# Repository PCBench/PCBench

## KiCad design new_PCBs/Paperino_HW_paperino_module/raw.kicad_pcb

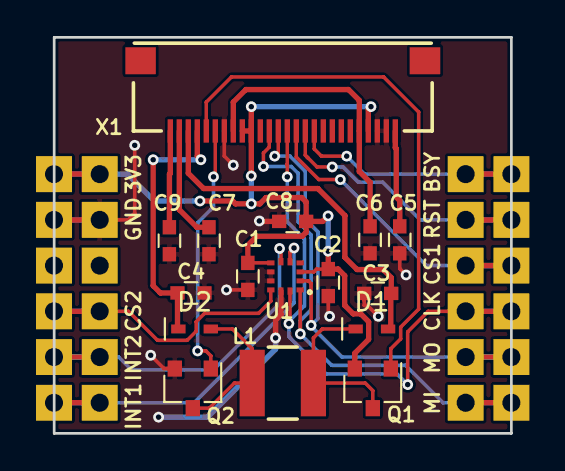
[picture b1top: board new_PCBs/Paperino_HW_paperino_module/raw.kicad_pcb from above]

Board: 2 copper layers, 25.4 x 22.0 mm, 20 parts (0 on the bottom side), 21 nets.

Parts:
C1, C2, C5: 100n; C_0603
C3, C4: 2µ2; C_0603
C6, C7, C8, C9: 1µ; C_0603
D1, D2: 30V; SOD-523F
L1: 47µ; NR4018T470M
P1, P2, P3, P4: CONN_01X06; 1x6_header
Q1: PMOS; SOT-23
Q2: NMOS; SOT-23
U1: BMA250E; LGA-12-2x2x0.95
X1: XF2M-2615-1A

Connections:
+3V3: C1.1, C2.2, C8.1, P2.1, P4.1, Q1.2, U1.3, U1.7, X1.4, X1.17, X1.18
/GDR_N: Q2.1, X1.21
/GDR_P: Q1.1, X1.22
/INT1: P2.6, P4.6, U1.5
/INT2: P2.5, P4.5, U1.6
/SPI_CLK: P1.3, P3.3, U1.12, X1.13
/SPI_CS1: P1.4, P3.4, X1.12
/SPI_CS2: P2.4, P4.4, U1.10
/SPI_MISO: P1.1, P3.1, U1.1, X1.15
/SPI_MOSI: P1.2, P3.2, U1.2, X1.14
/TPCOM: C5.1, X1.1
/VDD: C6.1, X1.5, X1.19
/VGH: C4.2, D2.1, X1.23
/VGL: C3.1, D1.2, X1.24
/VSH: C7.1, X1.25
/VSL: C9.1, X1.26
/~BUSY: P1.6, P3.6, X1.10
/~RST: P1.5, P3.5, X1.11
GND: C1.2, C2.1, C3.2, C4.1, C5.2, C6.2, C7.2, C8.2, C9.2, P2.2, P4.2, Q2.2, U1.8, U1.9, U1.11, X1.2, X1.3, X1.20
unnamed: D1.1, L1.1, Q1.3
unnamed: D2.2, L1.2, Q2.3

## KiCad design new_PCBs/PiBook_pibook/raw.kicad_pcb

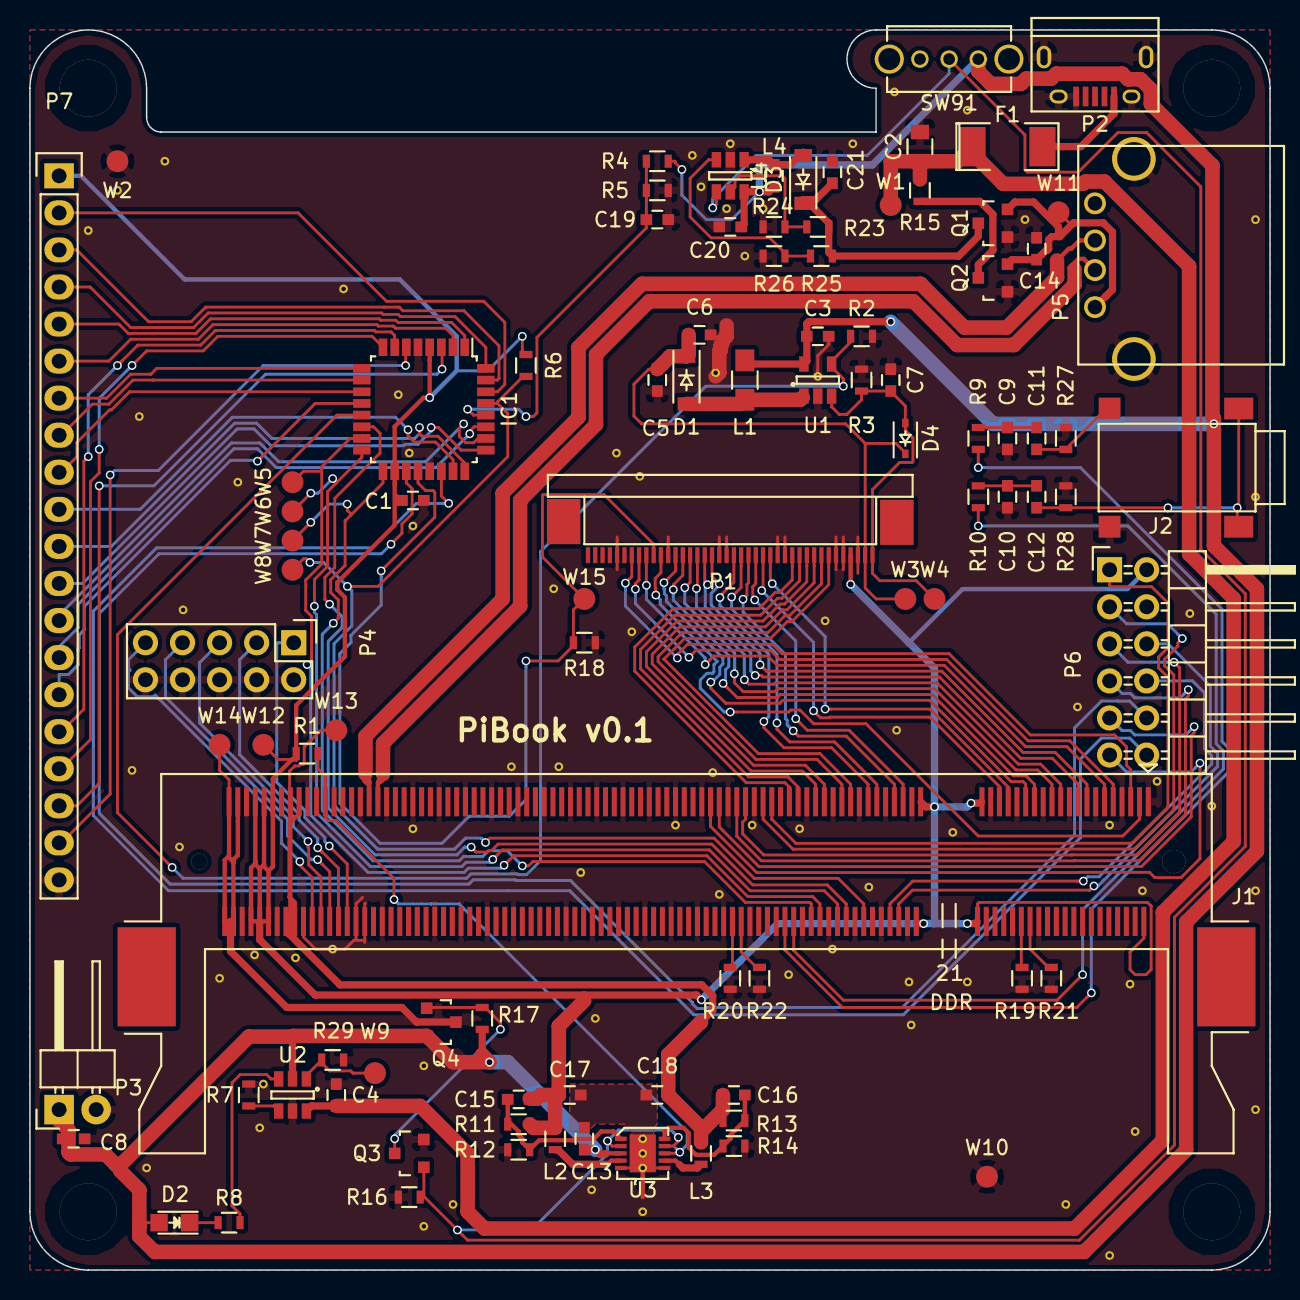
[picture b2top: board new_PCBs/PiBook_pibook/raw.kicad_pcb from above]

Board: 2 copper layers, 85.0 x 85.0 mm, 98 parts (0 on the bottom side), 103 nets.

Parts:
C1, C4, C5, C6, C7, C8, C11, C12, C20, C21: 1u; C_0603
C2: 22u; C_0805
C3: 4.7u; C_0603
C9, C10: 82n; C_0603
C13, C14, C17, C18: 10u; C_0603
C15, C16: 18p; C_0603
C19: 100n; C_0603
D1, D3: MBR0540T3G; SOD-123
D2: LED; LED_0805
D4: MM32Z24VT1G; SOD-323
F1: 2A; SMD-2010_Pol
IC1: ATTINY48-A; LQFP-32_7x7mm_Pitch0.8mm
J1: ComputeModule; Socket_SODIMM_DDR1-2_TE_1612618
J2: TRS_JACK_3PIN; TRS_3_SMD
L1: 6.8u; R_0805_HandSoldering
L2, L3: 2.2u; R_0603
L4: 10u; C_0603
MH1, MH2, MH3, MH4: Mounting_Hole; Mounting_hole_M3.5
P1: CONN_01X40; FPC40_BOTTOM
P2: USB_OTG; USB_Micro-B
P3: CONN_01X02; Pin_Header_Angled_1x02
P4: CONN_02X05; Pin_Header_Straight_2x05
P5: USB_A
P6: CONN_02X06; Pin_Header_Angled_2x06
P7: CONN_01X20; Pin_Header_Straight_1x20
Q1, Q2, Q4: Si2323DS; SOT-23
Q3: BSS138P; SOT-23
R1, R2, R4, R5, R6, R12, R14, R16, R17, R18, R19, R20, R21, R22, R27, R28: 100k; R_0603
R3: 12; R_0603
R7: 680; R_0603
R8: R; R_0603
R9, R10: 100; R_0603
R11: 450k; R_0603
R13: 200k; R_0603
R15: 0; R_0603
R23: 47k; R_0603
R24, R26, R29: 10k; R_0603
R25: 40k; R_0603
SW91: SPST; SPDT_SLIDE_SWITCH
TP1: Tie_point; tiepoint-0.3
U1: FAN5333; SOT-23-5
U2: BQ21040; SOT-23-6
U3: NCP1532; UDFN-10
U4: MIC2619YD6; SOT-23-6
W1: USB_VIN+; Measurement_Point_Round-SMD-Pad_Small
W2: USB_VIN-; Measurement_Point_Round-SMD-Pad_Small
W3: BACKL_A; Measurement_Point_Round-SMD-Pad_Small
W4: BACKL_K; Measurement_Point_Round-SMD-Pad_Small
W5, W6, W7, W8, W15: TEST_1P; Measurement_Point_Round-SMD-Pad_Small
W9: TS; Measurement_Point_Round-SMD-Pad_Small
W10: GND; Measurement_Point_Round-SMD-Pad_Small
W11: VUSB_OUT; Measurement_Point_Round-SMD-Pad_Small
W12: +3V3; Measurement_Point_Round-SMD-Pad_Small
W13: +1V8; Measurement_Point_Round-SMD-Pad_Small
W14: CM_VBAT; Measurement_Point_Round-SMD-Pad_Small

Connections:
+1V8: C16.1, C18.1, J1.183, J1.184, J1.185, J1.186, L3.2, R13.1, W13.1
+3V3: C1.1, C15.1, C17.1, IC1.4, IC1.18, J1.2, J1.39, J1.40, J1.41, J1.42, J1.189, J1.190, J1.191, J1.192, J1.193, J1.194, L2.2, P1.4, P6.2, P7.1, R1.1, R6.1, R11.1, W12.1
+5V: C21.1, D3.1, Q1.3, R23.1, R25.1
+BATT: C3.1, C8.1, C13.1, C20.1, D2.2, L1.1, L4.1, P3.1, Q4.2, R4.1, R17.1, SW91.1, U1.5, U2.2, U3.3, U4.6
+VUSB_IN: C2.1, C4.1, F1.1, R15.2, U2.6, W1.1
+VUSB_OUT: C14.1, P5.1, Q1.2, Q2.2, W11.1
/ANALOG0: IC1.19, P6.10
/ANALOG1: IC1.22, P6.12
/AUDIO_L_PWM: J1.70, R10.2
/AUDIO_R_PWM: J1.72, R9.2
/AVR_MISO: IC1.16, J1.60, W6.1
/AVR_MOSI: IC1.15, J1.64, W5.1
/AVR_SCK: IC1.17, J1.66, W7.1
/AVR_~CS: IC1.14, J1.58
/AVR_~RST: IC1.29, J1.54, R6.2, W8.1
/BACKL_A: C5.1, C6.1, D1.1, D4.1, P1.2, W3.1
/BACKL_K: C7.1, D4.2, P1.1, R3.1, U1.3, W4.1
/BACKL_PWM: IC1.13, R2.1, U1.4
/CM_RUN: J1.177, R1.2, U3.8
/CM_VBAT: J1.197, J1.198, J1.199, J1.200, Q4.3, W14.1
/KEY_C0: IC1.30, P7.2
/KEY_C1: IC1.31, P7.3
/KEY_C2: IC1.32, P7.4
/KEY_C3: IC1.1, P7.5
/KEY_C4: IC1.2, P7.6
/KEY_C5: IC1.9, P7.7
/KEY_C6: IC1.10, P7.8
/KEY_C7: IC1.11, P7.9
/KEY_C8: IC1.23, P7.10
/KEY_C9: IC1.24, P7.11
/KEY_C10: IC1.25, P7.12
/KEY_C11: IC1.26, P7.13
/KEY_R0: IC1.27, P7.14
/KEY_R1: IC1.12, P7.15
/KEY_R2: IC1.7, P7.16
/KEY_R3: IC1.8, P7.17
/KEY_R4: IC1.3, P7.18
/KEY_R5: IC1.6, P7.19
/LCD_B_2: J1.15, P1.23
/LCD_B_3: J1.17, P1.24
/LCD_B_4: J1.21, P1.25
/LCD_B_5: J1.23, P1.26
/LCD_B_6: J1.27, P1.27
/LCD_B_7: J1.29, P1.28
/LCD_CLK: J1.3, P1.30
/LCD_DEN: J1.5, P1.34
/LCD_DISP_ON: IC1.20, P1.31, R18.1, W15.1
/LCD_G_2: J1.33, P1.15
/LCD_G_3: J1.35, P1.16
/LCD_G_4: J1.45, P1.17
/LCD_G_5: J1.47, P1.18
/LCD_G_6: J1.51, P1.19
/LCD_G_7: J1.53, P1.20
/LCD_HSYNC: J1.11, P1.32
/LCD_R_2: J1.57, P1.7
/LCD_R_3: J1.59, P1.8
/LCD_R_4: J1.63, P1.9
/LCD_R_5: J1.65, P1.10
/LCD_R_6: J1.69, P1.11
/LCD_R_7: J1.71, P1.12
/LCD_VSYNC: J1.9, P1.33
/PWR_ENABLE: Q3.1, R16.1, SW91.2, U3.2, U3.9, U4.4
/UART_RX: J1.48, P6.8
/UART_TX: J1.46, P6.6
/USB_D+: J1.165, P5.2
/USB_D-: J1.167, P5.3
/USER_IO_0: J1.75, P6.1
/USER_IO_1: J1.77, P6.3
/USER_IO_2: J1.81, P6.5
/USER_IO_3: J1.83, P6.7
/USER_IO_4: J1.87, P6.9
/USER_IO_5: J1.89, P6.11
/VC_TCK: J1.180, P4.9
/VC_TDI: J1.174, P4.3
/VC_TDO: J1.178, P4.5
/VC_TMS: J1.176, P4.7
/VC_TRST_N: J1.172, P4.1
GND: C1.2, C2.2, C3.2, C4.2, C5.2, C6.2, C7.2, C8.2, C9.2, C10.2, C14.2, C19.2, C20.2, C21.2, IC1.5, IC1.21, J1.1, J1.7, J1.13, J1.19, J1.25, J1.26, J1.31, J1.32, J1.37, J1.38, J1.43, J1.44, J1.49, J1.50, J1.55, J1.56, J1.61, J1.62, J1.67, J1.68, J1.73, J1.74, J1.79, J1.80, J1.85, J1.86, J1.91, J1.92, J1.97, J1.98, J1.103, J1.104, J1.109, J1.110, J1.115, J1.116, J1.121, J1.122, J1.127, J1.133, J1.134, J1.139, J1.140, J1.145, J1.146, J1.151, J1.152, J1.157, J1.163, J1.164, J1.168, J1.169, J1.170, J1.181, J1.182, J1.187, J1.188, J1.195, J1.196, J2.2, P1.3, P1.5, P1.6, P1.13, P1.14, P1.21, P1.22, P1.29, P1.36, P2.5, P2.6, P3.2, P4.2, P4.4, P4.6, P4.8, P4.10, P5.4, P5.5, P6.4, P7.20, Q1.1, Q2.1, Q3.2, R2.2, R3.2, R5.2, R7.1, R12.2, R14.2, R16.2, R18.2, R19.2, R20.2, R21.2, R22.2, R24.2, R26.2, R27.2, R28.2, R29.1, TP1.2, U1.2, U2.5, U4.2, W2.1, W10.1
GNDPWR: C13.2, C17.2, C18.2, TP1.1, U3.5, U3.6
unnamed: C10.1, C12.1, R10.1
unnamed: C9.1, C11.1, R9.1
unnamed: C11.2, J2.3, R27.1
unnamed: C12.2, J2.1, R28.1
unnamed: C15.2, R11.2, R12.1, U3.1
unnamed: C16.2, R13.2, R14.1, U3.10
unnamed: C19.1, IC1.28, R4.2, R5.1
unnamed: D1.2, L1.2, U1.1
unnamed: D2.1, R8.1
unnamed: D3.2, L4.2, U4.1
unnamed: F1.2, P2.1
unnamed: J1.28, R21.1
unnamed: J1.30, R19.1
unnamed: J1.82, R22.1
unnamed: J1.84, R20.1
unnamed: L2.1, U3.4
unnamed: L3.1, U3.7
unnamed: Q2.3, R15.1
unnamed: Q3.3, Q4.1, R17.2
unnamed: R7.2, U2.4
unnamed: R8.2, U2.3
unnamed: R23.2, R24.1, U4.5
unnamed: R25.2, R26.1, U4.3
unnamed: R29.2, U2.1, W9.1

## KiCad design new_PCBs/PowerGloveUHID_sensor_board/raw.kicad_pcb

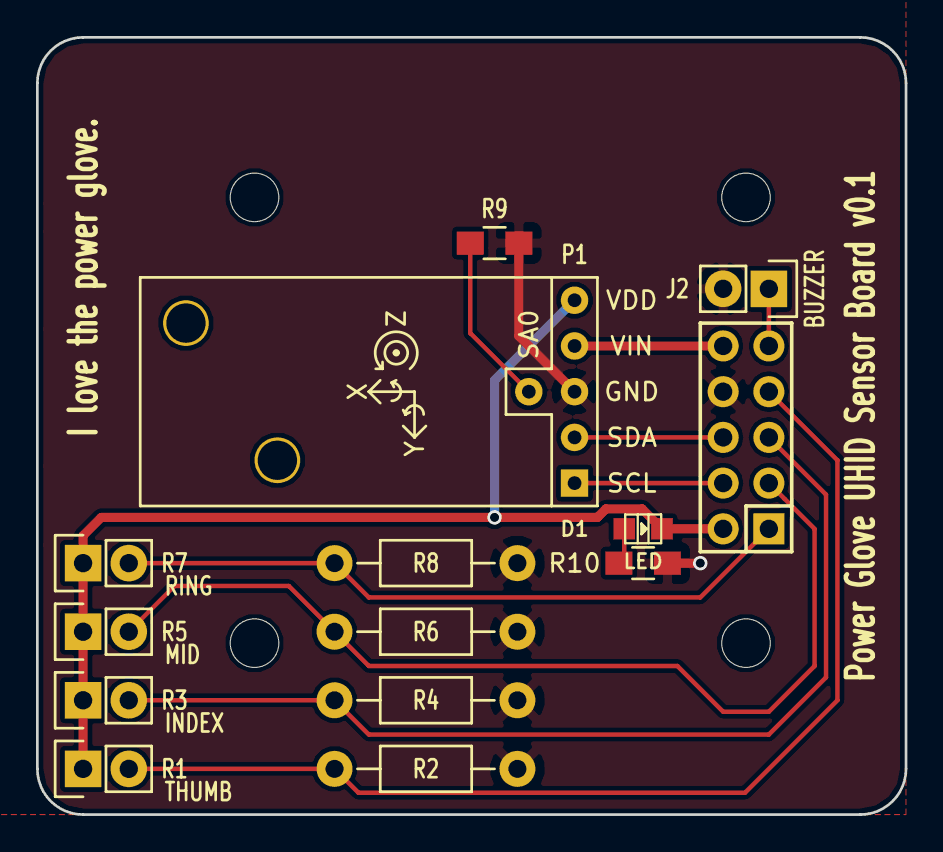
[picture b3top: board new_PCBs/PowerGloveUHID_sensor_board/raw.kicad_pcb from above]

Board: 2 copper layers, 48.3 x 43.2 mm, 14 parts (1 on the bottom side), 12 nets.

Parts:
D1: LED; Led_0805
J1: HEADER_5x2; Socket_Strip_Straight_2x05
J2: HEADER_2; Socket_Strip_Straight_1x02
P1: CONN_01X06; ALTIMU10
R1, R3, R5, R7: PG_FLEX; Socket_Strip_Straight_1x02
R2, R4, R6, R8: 1M; Resistor_Horizontal_RM10mm
R9: DNP; R_0805_HandSoldering
R10: 1k; R_0805_HandSoldering

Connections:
+3V3: D1.2, J1.2, P1.5, R1.1, R3.1, R5.1, R7.1
/BUZZER: J1.9, J2.1
/FLEX_INDEX: J1.5, R3.2, R4.1
/FLEX_MIDDLE: J1.3, R5.2, R6.1
/FLEX_RING: J1.1, R7.2, R8.1
/FLEX_THUMB: J1.7, R1.2, R2.1
/IMU_SCL: J1.4, P1.1
/IMU_SDA: J1.6, P1.2
/VIN: J1.10, P1.4
GND: J1.8, J2.2, P1.3, R2.2, R4.2, R6.2, R8.2, R9.1, R10.1
unnamed: D1.1, R10.2
unnamed: P1.6, R9.2

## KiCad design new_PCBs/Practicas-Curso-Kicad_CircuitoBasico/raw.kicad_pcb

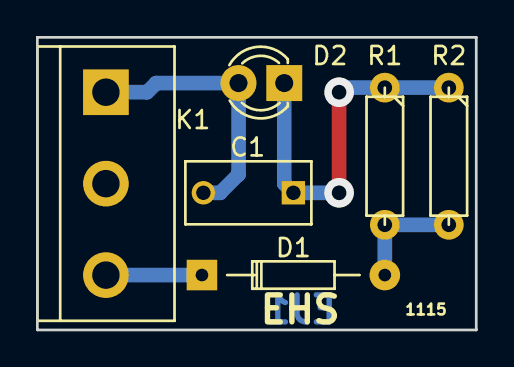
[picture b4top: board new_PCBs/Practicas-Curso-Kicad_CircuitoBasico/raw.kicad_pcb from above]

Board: 2 copper layers, 24.4 x 16.3 mm, 6 parts (0 on the bottom side), 4 nets.

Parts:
C1: 100nF; C_Rect_L7_W3.5_P5
D1: 1N4148; Diode_DO-35_SOD27_Horizontal_RM10
D2: LED ROJO; LED-3MM
K1: CONN_3; bornier3
R1, R2: 100K; R3-LARGE_PADS

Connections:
unnamed: C1.1, D2.1, R1.1, R2.1
unnamed: C1.2, D2.2, K1.1
unnamed: D1.1, K1.3
unnamed: D1.2, R1.2, R2.2

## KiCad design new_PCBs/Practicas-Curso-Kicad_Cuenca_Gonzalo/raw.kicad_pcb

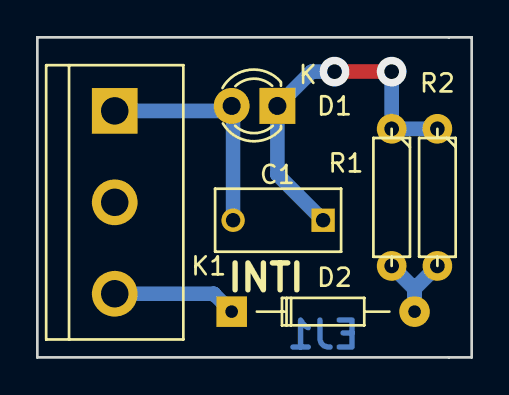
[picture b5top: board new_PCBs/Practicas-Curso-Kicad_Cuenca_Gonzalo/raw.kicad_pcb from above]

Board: 2 copper layers, 24.1 x 17.8 mm, 6 parts (0 on the bottom side), 4 nets.

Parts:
C1: 100nF; C_Rect_L7_W3.5_P5
D1: LED ROJO; LED-3MM
D2: 1N4148; Diode_DO-35_SOD27_Horizontal_RM10
K1: CONN_3; bornier3
R1, R2: 100k; R3-LARGE_PADS

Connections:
unnamed: C1.1, D1.1, R1.1, R2.1
unnamed: C1.2, D1.2, K1.1
unnamed: D2.1, K1.3
unnamed: D2.2, R1.2, R2.2
